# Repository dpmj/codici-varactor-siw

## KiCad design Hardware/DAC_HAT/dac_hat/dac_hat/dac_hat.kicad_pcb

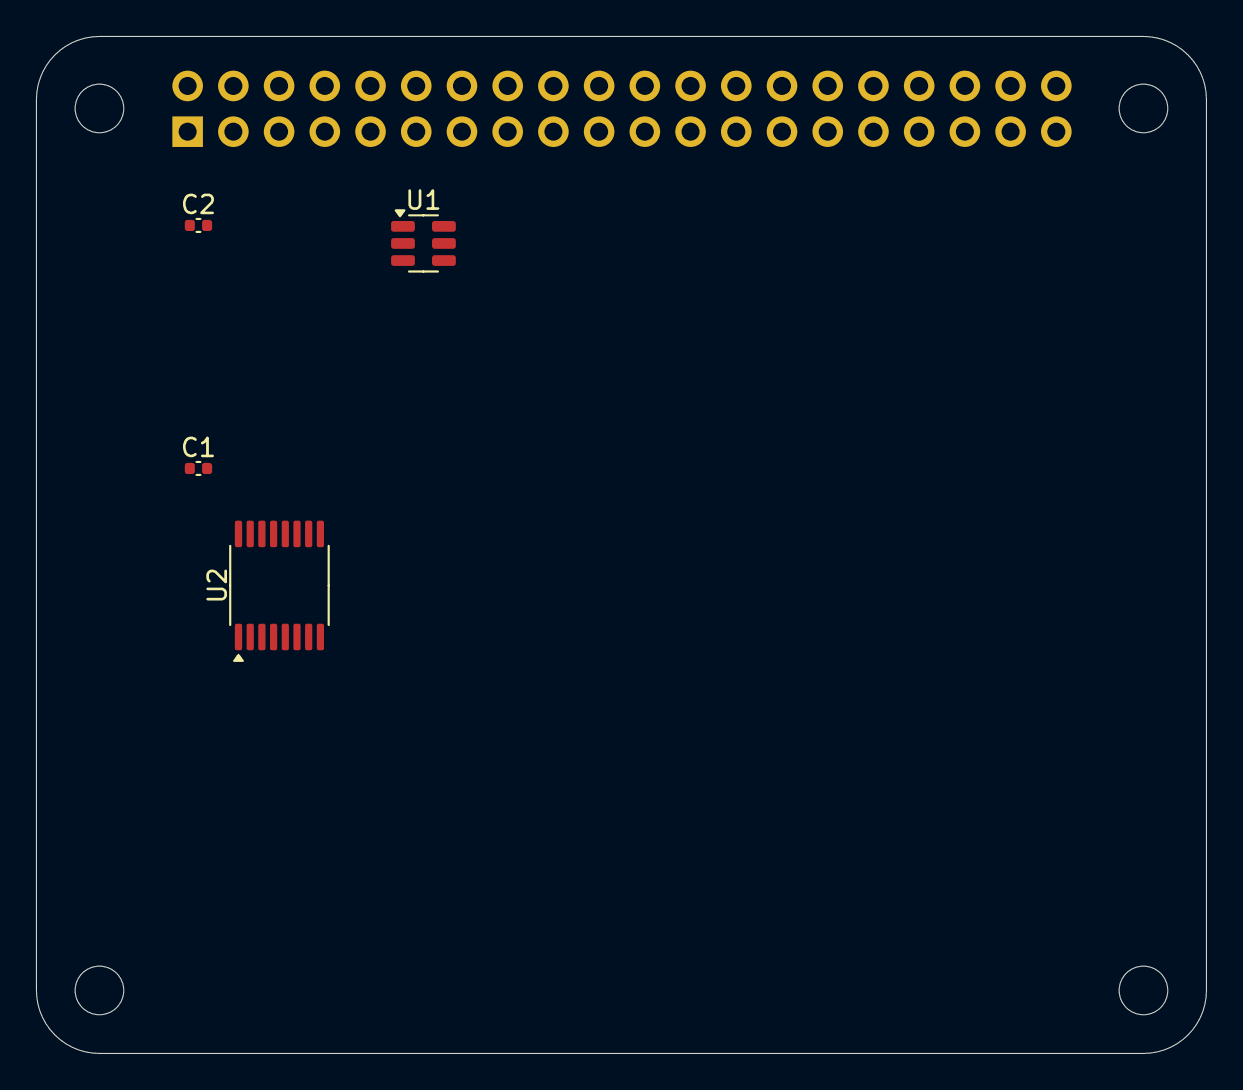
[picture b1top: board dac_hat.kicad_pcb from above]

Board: 4 copper layers, 65.0 x 56.5 mm, 9 parts (1 on the bottom side), 10 nets, no tracks yet.

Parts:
C1, C2: 100nF; C_0402_1005Metric
H1, H2, H3, H4: MountingHole; MountingHole_2.7mm
J1: Raspberry_Pi_2_3; PinSocket_2x20_P2.54mm_Vertical
U1: TLV61046ADB; SOT-23-6
U2: AD5504; TSSOP-16_4.4x5mm_P0.65mm

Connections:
/CLR: J1.29 (GCLK1/GPIO5), U2.1 (~CLR)
/LDAC: J1.22 (GPIO25), U2.8 (~LDAC)
/SCLK: J1.23 (SCLK0/GPIO11), U2.3 (SCLK)
/SDI: J1.19 (MOSI0/GPIO10), U2.4 (SDI)
/SDO: J1.21 (MISO0/GPIO9), U2.5 (SDO)
/SYNC: J1.26 (~CE1/GPIO7), U2.2 (~SYNC)
GND: C1.2, C2.2, J1.6 (GND), J1.9 (GND), J1.14 (GND), J1.20 (GND), J1.25 (GND), J1.30 (GND), J1.34 (GND), J1.39 (GND), U2.6 (DGND), U2.7 (AGND)
VCC_3V3: C1.1, J1.1 (3V3), J1.17 (3V3), U2.16 (V_{LOGIC})
VCC_5V: C2.1, J1.2 (5V), J1.4 (5V)
VCC_28V: U1.5 (VOUT), U2.14 (V_{DD})

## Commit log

2024-02-20 doing some progress
2024-02-21 Improved logging, results saving, console output. Created historic, s2p, log files. Callback function in opt.
2024-02-21 solving a few bugs
2024-02-21 oops
2024-02-22 vna variable was local
2024-02-22 solved bugs
2024-02-22 Maybe spi now works
2024-02-22 testing
2024-02-23 added dac testing
2024-02-27 testing DAC
2024-11-19 progress -- the dac works
2024-11-28 tests done, working
2024-11-28 i forgor
